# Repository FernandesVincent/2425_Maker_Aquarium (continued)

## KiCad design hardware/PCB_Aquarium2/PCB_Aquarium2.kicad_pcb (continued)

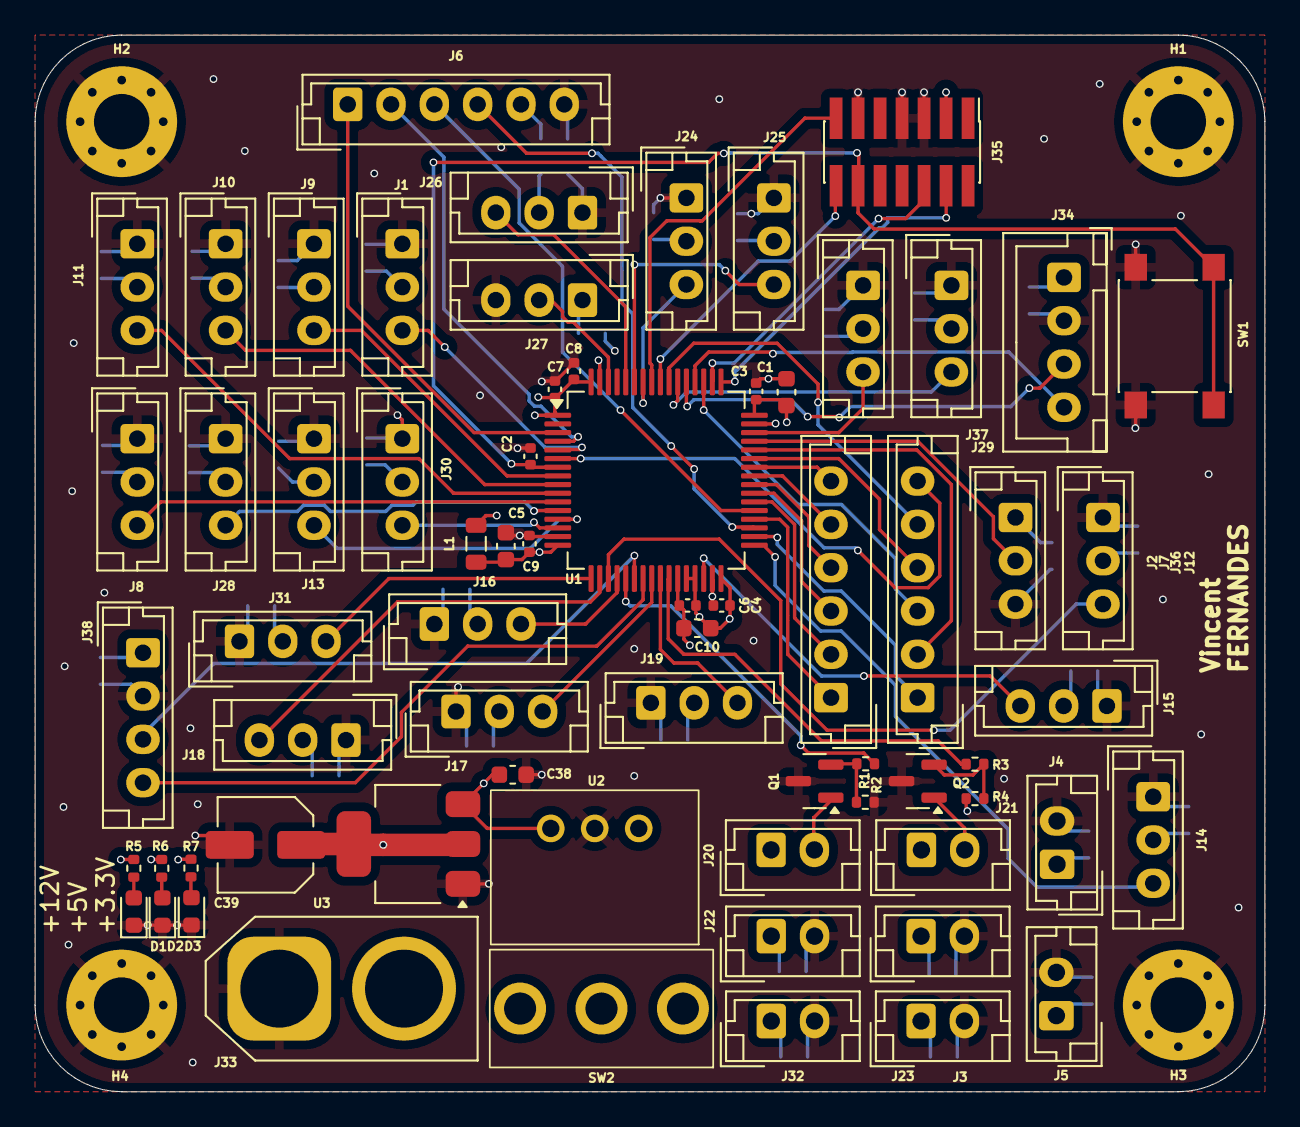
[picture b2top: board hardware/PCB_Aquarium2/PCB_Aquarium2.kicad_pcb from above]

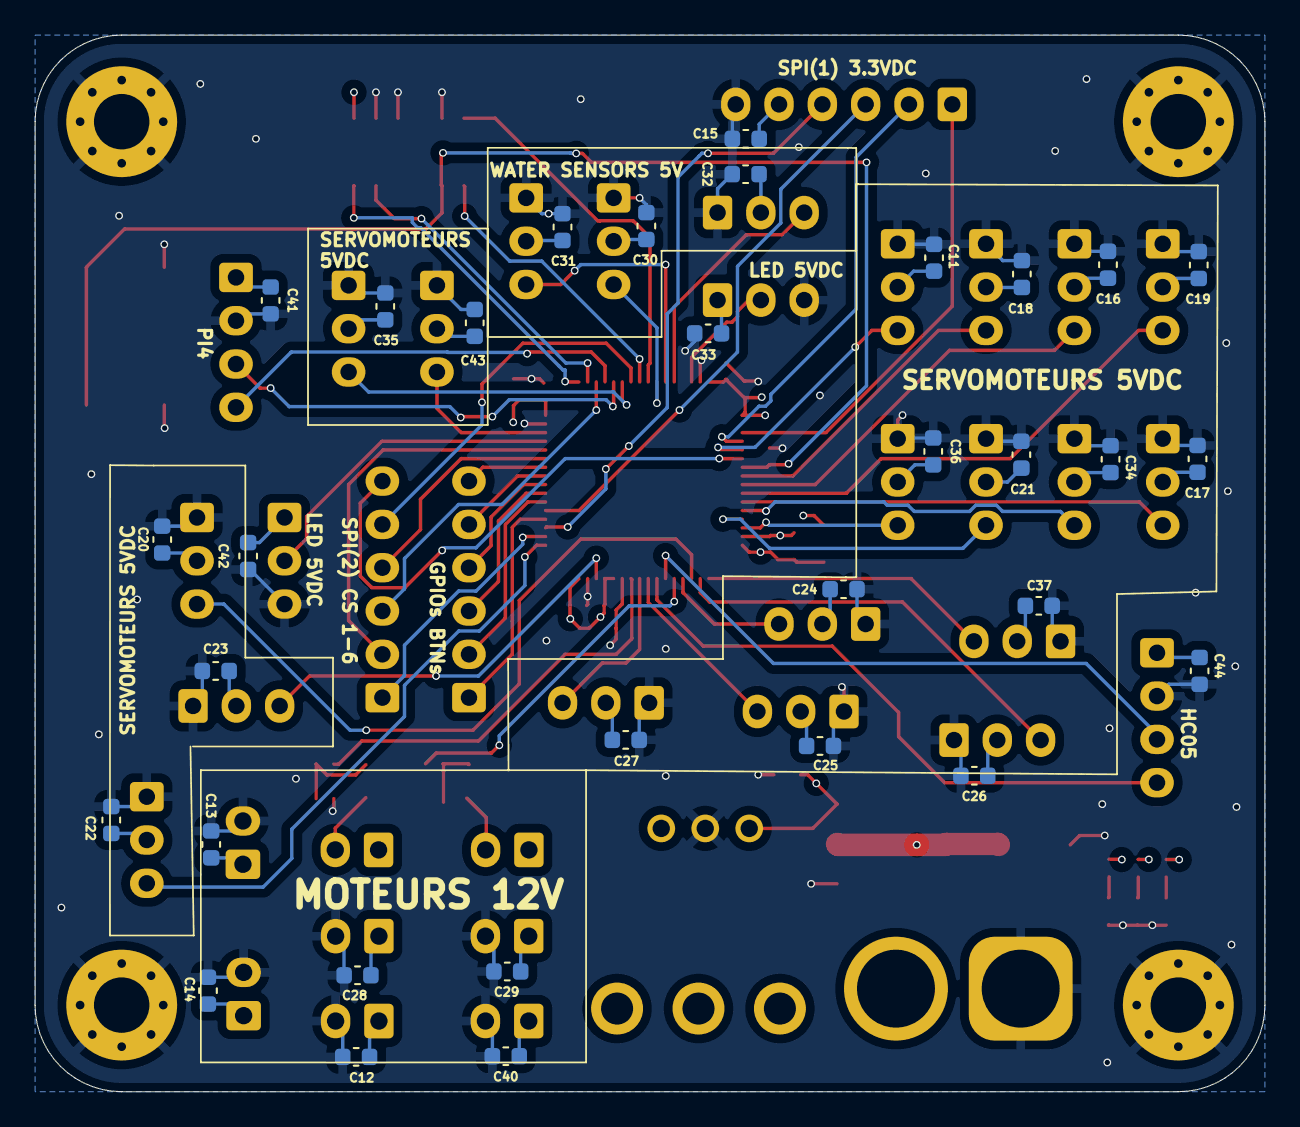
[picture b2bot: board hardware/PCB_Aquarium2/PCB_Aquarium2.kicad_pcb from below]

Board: 4 copper layers, 71.0 x 61.0 mm, 104 parts (32 on the bottom side), 62 nets.

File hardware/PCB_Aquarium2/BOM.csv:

"Reference","Qty","Value","Footprint","MPN"
"C1","1","4u7","Capacitor_SMD:C_0603_1608Metric",""
"C2,C3,C4,C6,C7,C8","6","100n","Capacitor_SMD:C_0402_1005Metric",""
"C5,C10,C11,C12,C13,C14,C15,C16,C17,C18,C19,C20,C21,C22,C23,C24,C25,C26,C27,C28,C29,C30,C31,C32,C33,C34,C35,C36,C37,C40,C41,C42,C43,C44","34","1u","Capacitor_SMD:C_0603_1608Metric",""
"C9","1","10n","Capacitor_SMD:C_0402_1005Metric",""
"C38","1","10u","Capacitor_SMD:C_0603_1608Metric",""
"C39","1","22u","Capacitor_SMD:C_Elec_5x5.4",""
"D1,D2,D3","3","RED_LED","LED_SMD:LED_0603_1608Metric","150060RS55040"
"H1,H2,H3,H4","4","MountingHole_Pad","MountingHole:MountingHole_3.2mm_M3_Pad_Via",""
"J1,J8,J9,J10,J11,J12,J13,J14,J15,J16,J17,J18,J19,J24,J25,J26,J27,J28,J29,J30,J31,J36,J37","23","Conn_01x03","Connector_JST:JST_EH_B3B-EH-A_1x03_P2.50mm_Vertical",""
"J2,J6,J7","3","Conn_01x06","Connector_JST:JST_EH_B6B-EH-A_1x06_P2.50mm_Vertical",""
"J3,J4,J5,J20,J21,J22,J23,J32","8","Conn_01x02","Connector_JST:JST_EH_B2B-EH-A_1x02_P2.50mm_Vertical",""
"J33","1","Conn_01x02","Connector_AMASS:AMASS_XT60-M_1x02_P7.20mm_Vertical",""
"J34","1","Conn_01x04","Connector_JST:JST_XH_B4B-XH-A_1x04_P2.50mm_Vertical",""
"J35","1","Conn_ST_STDC14","Connector_PinHeader_1.27mm:PinHeader_2x07_P1.27mm_Vertical_SMD","STLINK-V3MINIE"
"J38","1","Conn_01x04","Connector_JST:JST_EH_B4B-EH-A_1x04_P2.50mm_Vertical",""
"L1","1","39n","Inductor_SMD:L_0805_2012Metric",""
"Q1,Q2","2","NMOS","Package_TO_SOT_SMD:SOT-23","SQ2310ES"
"R1,R3","2","1k","Resistor_SMD:R_0402_1005Metric",""
"R2,R4","2","10k","Resistor_SMD:R_0402_1005Metric",""
"R5","1","5k1","Resistor_SMD:R_0402_1005Metric",""
"R6","1","1k6","Resistor_SMD:R_0402_1005Metric",""
"R7","1","820","Resistor_SMD:R_0402_1005Metric",""
"SW1","1","SW_SPST","mylib:SW_Push_1P1T_NO_6x6mm_H9.5mm",""
"SW2","1","SW_SPDT","mylib:472123010111","472123010111"
"U1","1","STM32G474RETx","Package_QFP:LQFP-64_10x10mm_P0.5mm",""
"U2","1","173010578","Library:173010542","173010578"
"U3","1","AZ1117-3.3","Package_TO_SOT_SMD:SOT-223-3_TabPin2","AZ1117CH2-3.3TRG1"

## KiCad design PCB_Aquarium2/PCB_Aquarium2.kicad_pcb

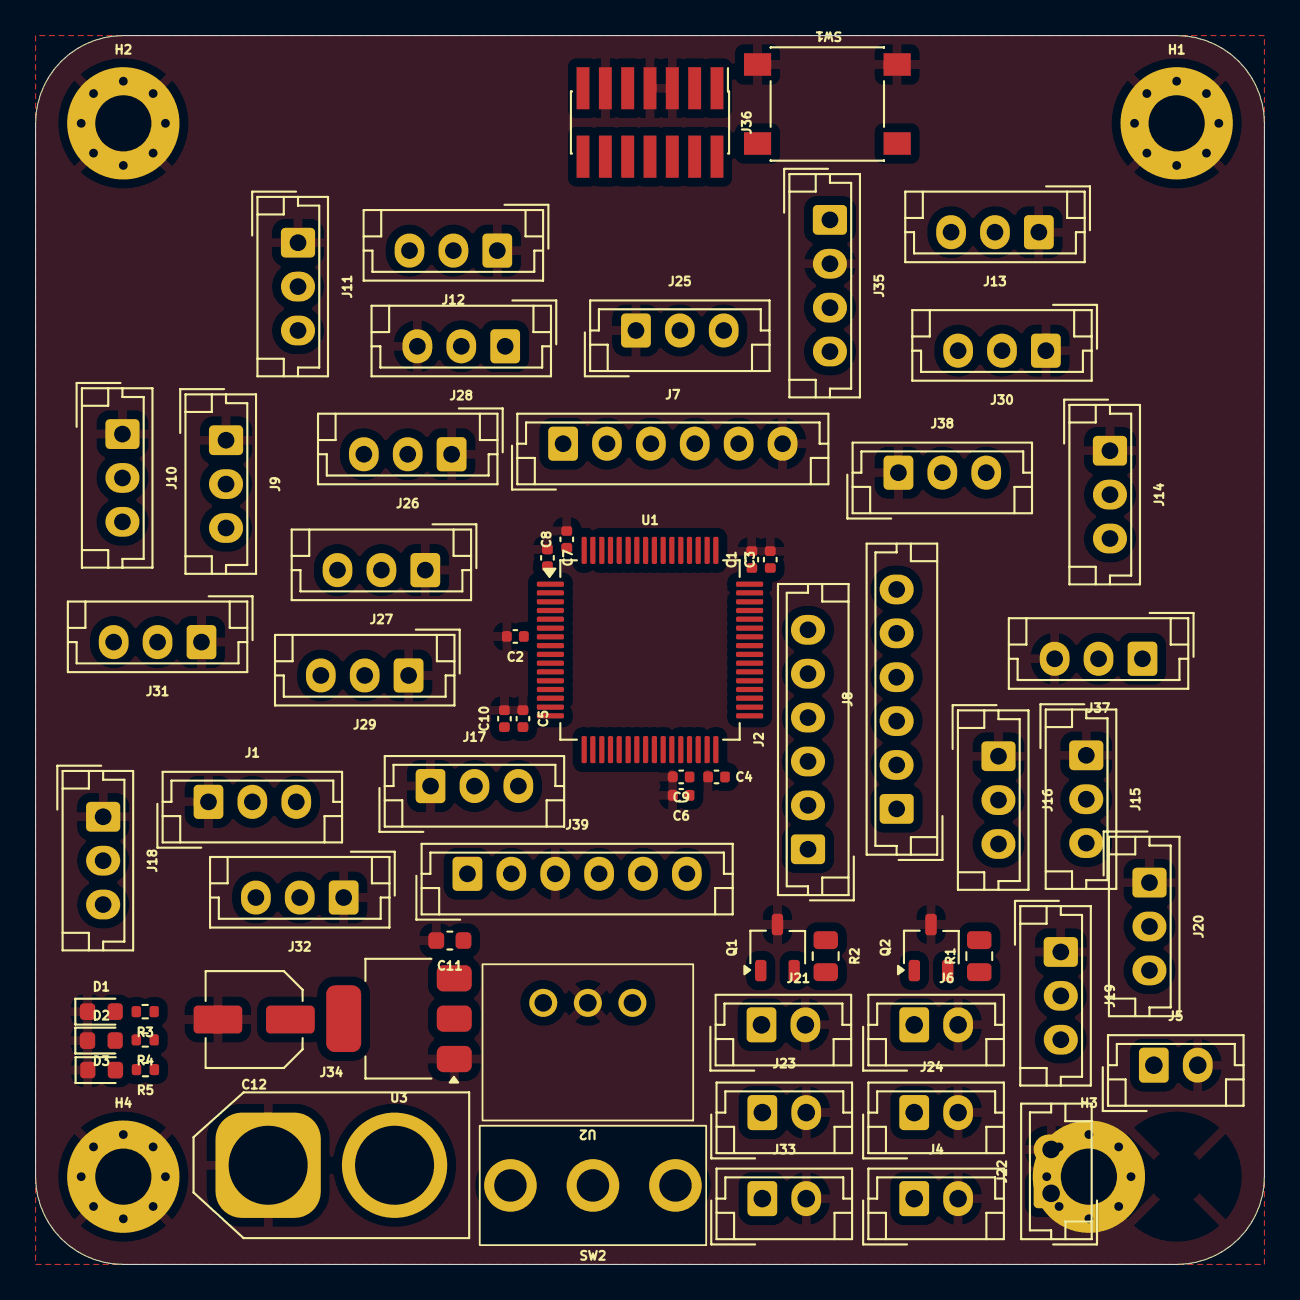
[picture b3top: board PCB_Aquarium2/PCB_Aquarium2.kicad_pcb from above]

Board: 4 copper layers, 70.0 x 70.0 mm, 69 parts (0 on the bottom side), 60 nets, no tracks yet.

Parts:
C1: 4u7; C_0402_1005Metric
C2, C3, C4, C6, C7, C8: 100n; C_0402_1005Metric
C5, C10: 1u; C_0402_1005Metric
C9: 10n; C_0402_1005Metric
C11: 10u; C_0603_1608Metric
C12: 22u; C_Elec_5x5.4
D1, D2, D3: RED_LED; LED_0603_1608Metric
H1, H2, H3, H4: MountingHole_Pad; MountingHole_3.2mm_M3_Pad_Via
J1, J9, J10, J11, J12, J13, J14, J15, J16, J17, J18, J19, J20, J25, J26, J27, J28, J29, J30, J31, J32, J37, J38: Conn_01x03; JST_EH_B3B-EH-A_1x03_P2.50mm_Vertical
J2, J7, J8, J39: Conn_01x06; JST_EH_B6B-EH-A_1x06_P2.50mm_Vertical
J4, J5, J6, J21, J22, J23, J24, J33: Conn_01x02; JST_EH_B2B-EH-A_1x02_P2.50mm_Vertical
J34: Conn_01x02; AMASS_XT60-M_1x02_P7.20mm_Vertical
J35: Conn_01x04; JST_EH_B4B-EH-A_1x04_P2.50mm_Vertical
J36: Conn_ST_STDC14; PinHeader_2x07_P1.27mm_Vertical_SMD
Q1, Q2: NPN; TSOT-23
R1, R2: 240; R_0805_2012Metric
R3: 5k1; R_0402_1005Metric
R4: 1k6; R_0402_1005Metric
R5: 820; R_0402_1005Metric
SW1: SW_SPST; SW_Push_1P1T_NO_6x6mm_H9.5mm
SW2: SW_SPDT; 472123010111
U1: STM32G474RETx; LQFP-64_10x10mm_P0.5mm
U2: 173010578; 173010542
U3: AZ1117-3.3; SOT-223-3_TabPin2

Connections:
+3.3V: C1.1, C3.1, C4.1, C5.2, C6.1, C7.2, C8.1, C9.1, C10.1, C12.1, J7.5, J25.2, J26.2, J27.2, J36.3 (VCC), R5.1, U1.1 (VBAT), U1.16 (VDD), U1.28 (VREF+), U1.29 (VDDA), U1.32 (VDD), U1.48 (VDD), U1.64 (VDD), U3.2 (VO)
+5V: C11.1, J1.2, J9.2, J10.2, J11.2, J12.2, J13.2, J14.2, J15.2, J16.2, J17.2, J18.2, J19.2, J20.2, J28.1, J29.2, J30.2, J31.2, J32.2, J35.1, J37.1, J38.2, J39.2, R4.1, U2.3 (Vout), U3.3 (VI)
+12V: J4.1, J5.1, J6.1, J21.1, J22.1, J23.1, J24.1, J33.1, Q1.1 (C), Q2.1 (C), R3.1, SW2.1 (A), U2.1 (Vin)
GND: C1.2, C2.2, C3.2, C4.2, C5.1, C6.2, C7.1, C8.2, C9.2, C10.2, C11.2, C12.2, D1.1 (K), D2.1 (K), D3.1 (K), H1.1, H2.1, H3.1, H4.1, J1.1, J4.2, J5.2, J6.2, J7.6, J9.1, J10.1, J11.1, J12.1, J13.1, J14.1, J15.1, J16.1, J17.1, J18.1, J19.1, J20.1, J21.2, J22.2, J23.2, J24.2, J25.1, J26.1, J27.1, J28.3, J29.1, J30.1, J31.1, J32.1, J33.2, J34.1, J35.2, J36.5 (GND), J36.7 (GND), J36.11 (GNDDetect), J37.3, J38.1, J39.3, Q1.3 (E), Q2.3 (E), SW1.2 (B), U1.15 (VSS), U1.27 (VSSA), U1.31 (VSS), U1.47 (VSS), U1.63 (VSS), U2.2 (GND), U3.1 (GND)
GPIO_BTN_1: J2.1, U1.38 (PC6)
GPIO_BTN_2: J2.2, U1.39 (PC7)
GPIO_BTN_3: J2.3, U1.40 (PC8)
GPIO_BTN_4: J2.4, U1.41 (PC9)
GPIO_BTN_5: J2.5, U1.36 (PB14)
GPIO_BTN_6: J2.6, U1.42 (PA8)
GPIO_D/C: J7.1, U1.3 (PC14)
GPIO_PH: J1.3, U1.2 (PC13)
GPIO_PUMP_1: R2.1, U1.21 (PA7)
GPIO_PUMP_2: R1.1, U1.26 (PB2)
GPIO_RES: J7.2, U1.4 (PC15)
GPIO_SPI_CS_1: J8.1, U1.34 (PB12)
GPIO_SPI_CS_2: J8.2, U1.43 (PA9)
GPIO_SPI_CS_3: J8.3, U1.51 (PA15)
GPIO_SPI_CS_4: J8.4, U1.44 (PA10)
GPIO_SPI_CS_5: J8.5, U1.55 (PD2)
GPIO_SPI_CS_6: J8.6, U1.6 (PF1)
GPIO_WaterSensor_1: J25.3, U1.58 (PB5)
GPIO_WaterSensor_2: J26.3, U1.59 (PB6)
GPIO_WaterSensor_3: J27.3, U1.60 (PB7)
NRST: C2.1, J36.12 (~RST), SW1.1 (A), U1.7 (PG10)
unnamed: D1.2 (A), R3.2
unnamed: D2.2 (A), R4.2
unnamed: D3.2 (A), R5.2
unnamed: J34.2, SW2.2 (B)
unnamed: Q1.2 (B), R2.2
unnamed: Q2.2 (B), R1.2
SPI2_MOSI: J7.3, U1.37 (PB15)
SPI2_SCK: J7.4, U1.35 (PB13)
SWCLK: J36.6 (JCLK/SWCLK), U1.50 (PA14)
SWDIO: J36.4 (JTMS/SWDIO), U1.49 (PA13)
TIM1_CH1_PWM: J10.3, U1.8 (PC0)
TIM1_CH2_PWM: J11.3, U1.9 (PC1)
TIM1_CH3_PWM: J12.3, U1.10 (PC2)
TIM1_CH4_PWM: J9.3, U1.11 (PC3)
TIM2_CH1_PWM: J13.3, U1.19 (PA5)
TIM2_CH2_PWM: J14.3, U1.13 (PA1)
TIM2_CH3_PWM: J15.3, U1.30 (PB10)
TIM2_CH4_PWM: J16.3, U1.33 (PB11)
TIM3_CH1_PWM: J17.3, U1.20 (PA6)
TIM3_CH2_PWM: J18.3, U1.18 (PA4)
TIM3_CH3_PWM: J19.3, U1.24 (PB0)
TIM3_CH4_PWM: J20.3, U1.25 (PB1)
TIM4_CH1_PWM: J37.2, U1.45 (PA11)
TIM4_CH2_PWM: J38.3, U1.46 (PA12)
TIM4_CH4_PWM: J28.2, U1.62 (PB9)
TIM5_CH1_PWM: J29.3, U1.12 (PA0)
TIM5_CH2_PWM: J30.3, U1.54 (PC12)
TIM5_CH3_PWM: J31.3, U1.14 (PA2)
TIM5_CH4_PWM: J32.3, U1.17 (PA3)
UART_DEBUG_RX: J36.13 (VCP_RX), U1.57 (PB4)
UART_DEBUG_TX: J36.14 (VCP_TX), U1.56 (PB3)
USART1_RX: J39.5, U1.23 (PC5)
USART1_TX: J39.4, U1.22 (PC4)
USART3_RX: J35.4, U1.53 (PC11)
USART3_TX: J35.3, U1.52 (PC10)

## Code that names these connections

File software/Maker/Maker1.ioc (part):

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Mcu.Name=STM32G474R(B-C-E)Tx
Mcu.Package=LQFP64
Mcu.UserName=STM32G474RETx
PA0.Signal=S_TIM5_CH1
PA1.Signal=S_TIM2_CH2
PA10.Signal=GPIO_Output
PA11.Signal=S_TIM4_CH1
PA12.Signal=S_TIM4_CH2
PA13.Mode=Serial_Wire
PA13.Signal=SYS_JTMS-SWDIO
PA14.Mode=Serial_Wire
PA14.Signal=SYS_JTCK-SWCLK
PA15.Signal=GPIO_Output
PA2.Signal=S_TIM5_CH3
PA3.Signal=S_TIM5_CH4
PA4.Signal=S_TIM3_CH2
PA5.Signal=S_TIM2_CH1
PA6.Signal=S_TIM3_CH1
PA7.Signal=GPIO_Output
PA8.Signal=GPIO_Input
PA9.Signal=GPIO_Output
PB0.Signal=S_TIM3_CH3
PB1.Signal=S_TIM3_CH4
PB10.Signal=S_TIM2_CH3
PB11.Signal=S_TIM2_CH4
PB12.Signal=GPIO_Output
PB13.Mode=TX_Only_Simplex_Unidirect_Master
PB13.Signal=SPI2_SCK
PB14.Signal=GPIO_Input
PB15.Mode=TX_Only_Simplex_Unidirect_Master
PB15.Signal=SPI2_MOSI
PB2.Signal=GPIO_Output
PB3.Mode=Asynchronous
PB3.Signal=USART2_TX
PB4.Mode=Asynchronous
PB4.Signal=USART2_RX
PB5.Signal=GPIO_Input
PB6.Signal=GPIO_Input
PB7.Signal=GPIO_Input
PB9.Signal=S_TIM4_CH4
PC0.Signal=S_TIM1_CH1
PC1.Signal=S_TIM1_CH2
PC10.Mode=Asynchronous
PC10.Signal=USART3_TX
PC11.Mode=Asynchronous
PC11.Signal=USART3_RX
PC12.Signal=S_TIM5_CH2
PC13.Signal=GPIO_Input
PC14-OSC32_IN.Signal=GPIO_Output
PC15-OSC32_OUT.Signal=GPIO_Output
PC2.Signal=S_TIM1_CH3
PC3.Signal=S_TIM1_CH4
PC4.Mode=Asynchronous
PC4.Signal=USART1_TX
PC5.Mode=Asynchronous
PC5.Signal=USART1_RX
PC6.Signal=GPIO_Input
PC7.Signal=GPIO_Input
PC8.Signal=GPIO_Input
PC9.Signal=GPIO_Input
PD2.Signal=GPIO_Output
PF0-OSC_IN.Mode=IN10-Single-Ended
PF0-OSC_IN.Signal=ADC1_IN10
PF1-OSC_OUT.Signal=GPIO_Output
RCC.HSE_VALUE=8000000
RCC.SYSCLKFreq_VALUE=16000000
board=custom

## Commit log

2025-01-21 onshape exercises
2025-03-11 Ajouté(e) Maker_Aquarium.drawio
2025-03-16 PCB-v0
2025-03-17 PCBs V1
2025-03-17 PCBs v2
2025-03-17 PCBs v3
2025-03-20 PCBs v4
2025-03-20 PCBs V5
2025-03-20 soft (ioc)
2025-03-20 Gerbers
2025-03-22 ajoutpremiers fichiers python et maj JST XH pour la PI4
2025-03-22 ajout des BOM
